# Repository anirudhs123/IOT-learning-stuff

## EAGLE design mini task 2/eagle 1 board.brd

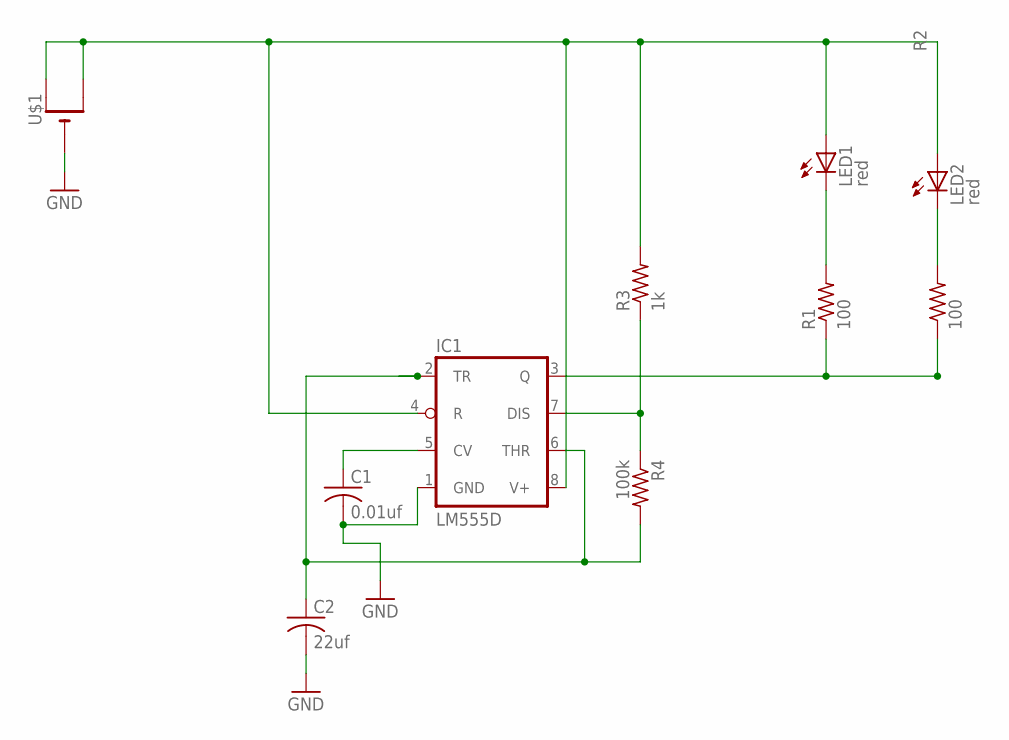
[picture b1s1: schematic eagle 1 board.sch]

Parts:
C1: 0.01uf; C0805
C2: 22uf; C0805
IC1: LM555D; SO08
LED1, LED2: red; CHIPLED_0805
R1, R2: 100; R0805
R3: 1k; R0805
R4: 100k; R0805
U$1: CR1220SMT; CR1220-SMD

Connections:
GND: C1.2, C2.2, IC1.1 (GND), U$1.-
unnamed: LED1.C, R1.2
unnamed: LED2.C, R2.2
unnamed: IC1.3 (Q), R1.1, R2.1
unnamed: IC1.7 (DIS), R3.1, R4.1
unnamed: C1.1, IC1.5 (CV)
unnamed: C2.1, IC1.2 (TR), IC1.6 (THR), R4.2
unnamed: IC1.4 (R), IC1.8 (V+), LED1.A, LED2.A, R3.2, U$1.+$1 (+), U$1.+$2 (+1)

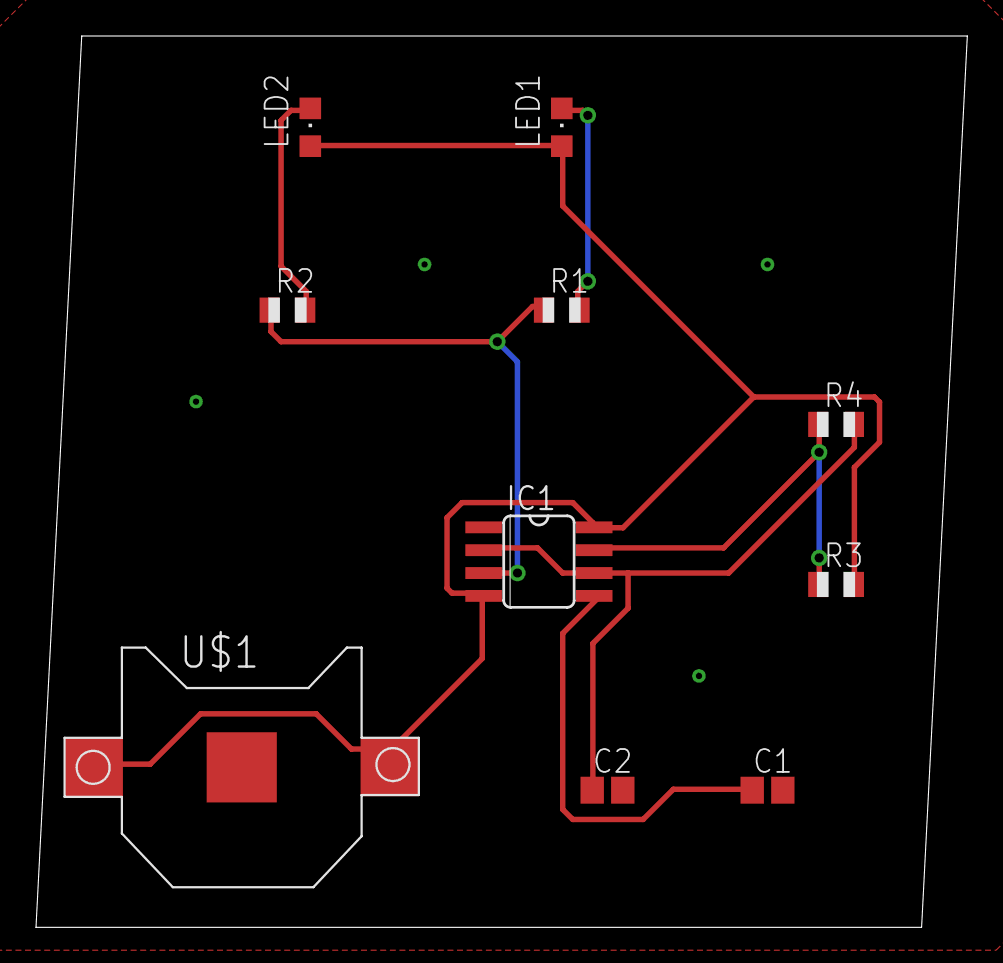
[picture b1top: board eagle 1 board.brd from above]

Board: 2 copper layers, 51.7 x 49.5 mm, 10 parts (0 on the bottom side), 8 nets.
